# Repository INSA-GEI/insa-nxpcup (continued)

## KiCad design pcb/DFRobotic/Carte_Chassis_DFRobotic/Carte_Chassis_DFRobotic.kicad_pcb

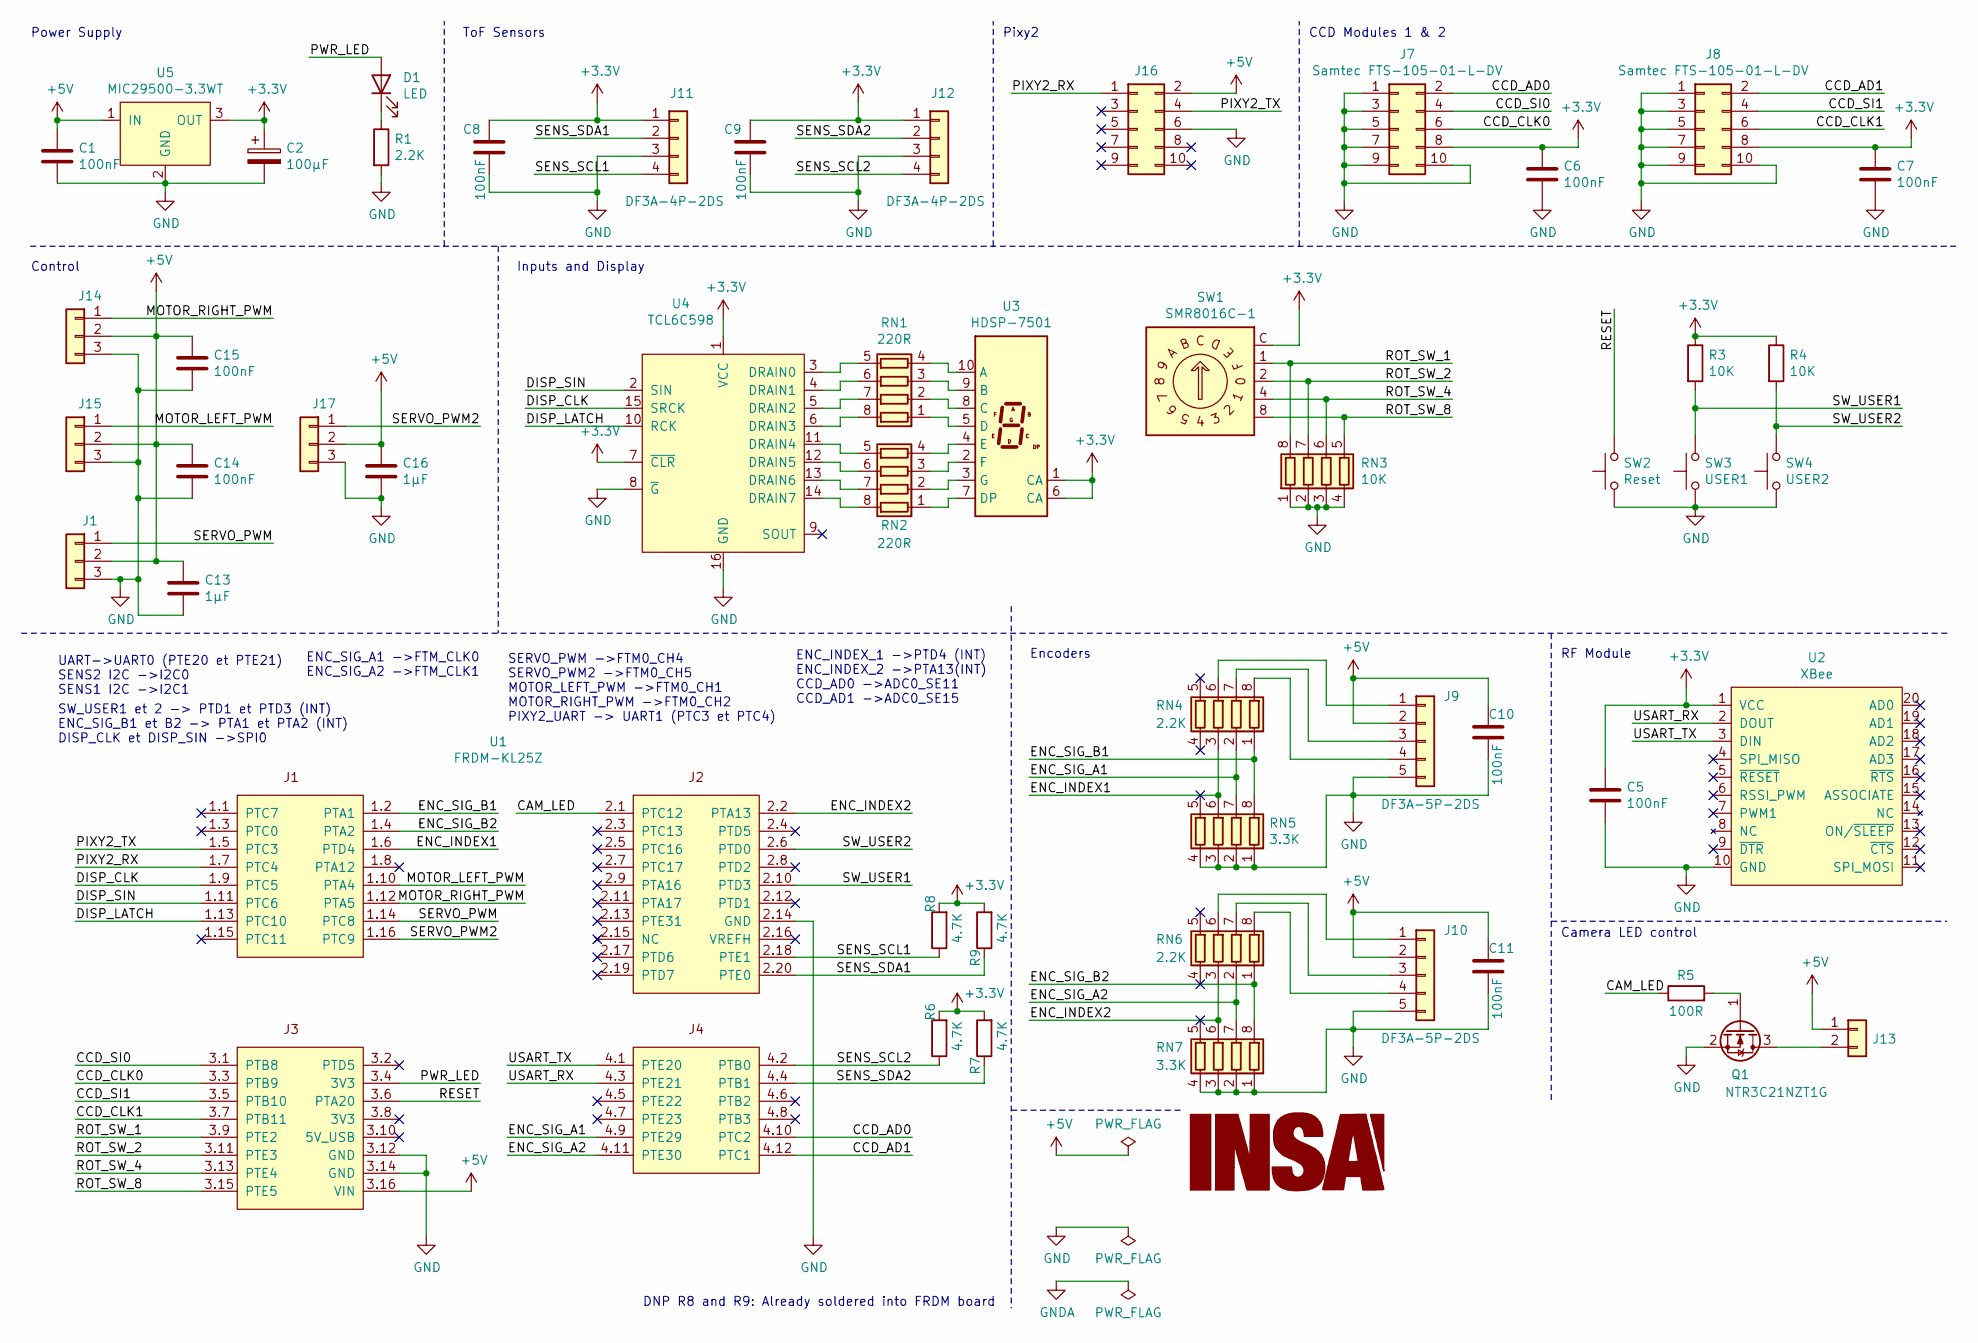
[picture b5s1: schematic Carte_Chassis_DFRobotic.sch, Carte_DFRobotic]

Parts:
C1, C5, C6, C7, C8, C9, C10, C11, C14, C15: 100nF; C_1206_3216Metric_Pad1.42x1.75mm_HandSolder
C2: 100µF; CP_Radial_D6.3mm_P2.50mm
C13, C16: 1µF; C_1206_3216Metric_Pad1.42x1.75mm_HandSolder
D1: LED; LED_1206_3216Metric_Pad1.42x1.75mm_HandSolder
J1, J14, J15, J17: Conn_01x03; PinHeader_1x03_P2.54mm_Horizontal
J7, J8: Samtec FTS-105-01-L-DV; PinHeader_2x05_P1.27mm_Vertical
J9, J10: DF3A-5P-2DS
J11, J12: DF3A-4P-2DS
J13: Conn_01x02; PinHeader_1x02_P2.54mm_Vertical
J16: Conn_02x05_Odd_Even; Multicomp_MC9A12-1034_2x05_P2.54mm_Vertical
Logo1: LOGO; insa-image
Q1: NTR3C21NZT1G; SOT-23
R1: 2.2K; R_1206_3216Metric_Pad1.42x1.75mm_HandSolder
R3, R4: 10K; R_1206_3216Metric_Pad1.42x1.75mm_HandSolder
R5: 100R; R_1206_3216Metric_Pad1.42x1.75mm_HandSolder
R6, R7, R8, R9: 4.7K; R_1206_3216Metric_Pad1.42x1.75mm_HandSolder
RN1, RN2: 220R; R_Array_Convex_4x0603
RN3: 10K; R_Array_Convex_4x0603
RN4, RN6: 2.2K; R_Array_Convex_4x0603
RN5, RN7: 3.3K; R_Array_Convex_4x0603
SW1: SMR8016C-1; Nidec_Copal_SMR-8016C
SW2: Reset; SW_PUSH_6mm_H4.3mm
SW3: USER1; SW_PUSH_6mm_H4.3mm
SW4: USER2; SW_PUSH_6mm_H4.3mm
U1: FRDM-KL25Z
U2: XBee; Xbee3
U3: HDSP-7501; HDSP-A151
U4: TCL6C598; TSSOP-16_4.4x5mm_P0.65mm
U5: MIC29500-3.3WT; TO-220-3_Vertical

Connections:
+3V3: C2.1, C5.1, C6.1, C7.1, C8.1, C9.1, J7.8, J8.8, J11.1, J12.1, R3.1, R4.1, R6.2, R7.2, R8.2, R9.2, SW1.C, U2.1 (VCC), U3.1 (CA), U3.6 (CA), U4.1 (VCC), U4.7 (~CLR), U5.3 (OUT)
+5V: C1.1, C10.1, C11.1, C13.1, C14.1, C15.1, C16.1, J1.2, J9.2, J10.2, J13.1, J14.2, J15.2, J16.2, J17.2, U1.3.16 (VIN), U5.1 (IN)
/CAM_LED: R5.1, U1.2.1 (PTC12)
/CCD_AD0: J7.2, U1.4.10 (PTC2)
/CCD_AD1: J8.2, U1.4.12 (PTC1)
/CCD_CLK0: J7.6, U1.3.3 (PTB9)
/CCD_CLK1: J8.6, U1.3.7 (PTB11)
/CCD_SI0: J7.4, U1.3.1 (PTB8)
/CCD_SI1: J8.4, U1.3.5 (PTB10)
/DISP_CLK: U1.1.9 (PTC5), U4.15 (SRCK)
/DISP_LATCH: U1.1.13 (PTC10), U4.10 (RCK)
/DISP_SIN: U1.1.11 (PTC6), U4.2 (SIN)
/ENC_INDEX1: RN4.3 (R3.1), RN5.6 (R3.2), U1.1.6 (PTD4)
/ENC_INDEX2: RN6.3 (R3.1), RN7.6 (R3.2), U1.2.2 (PTA13)
/ENC_SIG_A1: RN4.2 (R2.1), RN5.7 (R2.2), U1.4.9 (PTE29)
/ENC_SIG_A2: RN6.2 (R2.1), RN7.7 (R2.2), U1.4.11 (PTE30)
/ENC_SIG_B1: RN4.1 (R1.1), RN5.8 (R1.2), U1.1.2 (PTA1)
/ENC_SIG_B2: RN6.1 (R1.1), RN7.8 (R1.2), U1.1.4 (PTA2)
/MOTOR_LEFT_PWM: J15.1, U1.1.10 (PTA4)
/MOTOR_RIGHT_PWM: J14.1, U1.1.12 (PTA5)
/PIXY2_RX: J16.1, U1.1.7 (PTC4)
/PIXY2_TX: J16.4, U1.1.5 (PTC3)
/PWR_LED: D1.2 (A), U1.3.4 (3V3)
/RESET: SW2.2, U1.3.6 (PTA20)
/ROT_SW_1: RN3.8 (R1.2), SW1.1, U1.3.9 (PTE2)
/ROT_SW_2: RN3.7 (R2.2), SW1.2, U1.3.11 (PTE3)
/ROT_SW_4: RN3.6 (R3.2), SW1.4, U1.3.13 (PTE4)
/ROT_SW_8: RN3.5 (R4.2), SW1.8, U1.3.15 (PTE5)
/SENS_SCL1: J11.4, R8.1, U1.2.18 (PTE1)
/SENS_SCL2: J12.4, R6.1, U1.4.2 (PTB0)
/SENS_SDA1: J11.2, R9.1, U1.2.20 (PTE0)
/SENS_SDA2: J12.2, R7.1, U1.4.4 (PTB1)
/SERVO_PWM: J1.1, U1.1.14 (PTC8)
/SERVO_PWM2: J17.1, U1.1.16 (PTC9)
/SW_USER1: R3.2, SW3.2, U1.2.10 (PTD3)
/SW_USER2: R4.2, SW4.2, U1.2.6 (PTD0)
/USART_RX: U1.4.3 (PTE21), U2.2 (DOUT)
/USART_TX: U1.4.1 (PTE20), U2.3 (DIN)
GND: C1.2, C2.2, C5.2, C6.2, C7.2, C8.2, C9.2, C10.2, C11.2, C13.2, C14.2, C15.2, C16.2, J1.3, J7.1, J7.3, J7.5, J7.7, J7.9, J7.10, J8.1, J8.3, J8.5, J8.7, J8.9, J8.10, J9.5, J10.5, J11.3, J12.3, J14.3, J15.3, J16.6, J17.3, Q1.2 (S), R1.2, RN3.1 (R1.1), RN3.2 (R2.1), RN3.3 (R3.1), RN3.4 (R4.1), RN5.1 (R1.1), RN5.2 (R2.1), RN5.3 (R3.1), RN5.4 (R4.1), RN7.1 (R1.1), RN7.2 (R2.1), RN7.3 (R3.1), RN7.4 (R4.1), SW2.1, SW3.1, SW4.1, U1.2.14 (GND), U1.3.12 (GND), U1.3.14 (GND), U2.10 (GND), U4.8 (~G), U4.16 (GND), U5.2 (GND)
unnamed: D1.1 (K), R1.1
unnamed: J9.1, RN4.6 (R3.2)
unnamed: J9.3, RN4.7 (R2.2)
unnamed: J9.4, RN4.8 (R1.2)
unnamed: J10.1, RN6.6 (R3.2)
unnamed: J10.3, RN6.7 (R2.2)
unnamed: J10.4, RN6.8 (R1.2)
unnamed: J13.2, Q1.3 (D)
unnamed: Q1.1 (G), R5.2
unnamed: RN1.1 (R1.1), U3.5 (D)
unnamed: RN1.2 (R2.1), U3.8 (C)
unnamed: RN1.3 (R3.1), U3.9 (B)
unnamed: RN1.4 (R4.1), U3.10 (A)
unnamed: RN1.5 (R4.2), U4.3 (DRAIN0)
unnamed: RN1.6 (R3.2), U4.4 (DRAIN1)
unnamed: RN1.7 (R2.2), U4.5 (DRAIN2)
unnamed: RN1.8 (R1.2), U4.6 (DRAIN3)
unnamed: RN2.1 (R1.1), U3.7 (DP)
unnamed: RN2.2 (R2.1), U3.3 (G)
unnamed: RN2.3 (R3.1), U3.2 (F)
unnamed: RN2.4 (R4.1), U3.4 (E)
unnamed: RN2.5 (R4.2), U4.11 (DRAIN4)
unnamed: RN2.6 (R3.2), U4.12 (DRAIN5)
unnamed: RN2.7 (R2.2), U4.13 (DRAIN6)
unnamed: RN2.8 (R1.2), U4.14 (DRAIN7)

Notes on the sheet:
Power Supply
Control
Inputs and Display
CCD Modules 1 & 2
RF Module
Encoders
ToF Sensors
Camera LED control
DNP R8 and R9: Already soldered into FRDM board
UART->UART0 (PTE20 et PTE21) SENS2 I2C ->I2C0 SENS1 I2C ->I2C1
ENC_SIG_A1 ->FTM_CLK0 ENC_SIG_A2 ->FTM_CLK1
SERVO_PWM ->FTM0_CH4 SERVO_PWM2 ->FTM0_CH5 MOTOR_LEFT_PWM ->FTM0_CH1 MOTOR_RIGHT_PWM ->FTM0_CH2 PIXY2_UART -> UART1 (PTC3 et PTC4)
ENC_INDEX_1 ->PTD4 (INT) ENC_INDEX_2 ->PTA13(INT) CCD_AD0 ->ADC0_SE11 CCD_AD1 ->ADC0_SE15
SW_USER1 et 2 -> PTD1 et PTD3 (INT) ENC_SIG_B1 et B2 -> PTA1 et PTA2 (INT) DISP_CLK et DISP_SIN ->SPI0
Pixy2

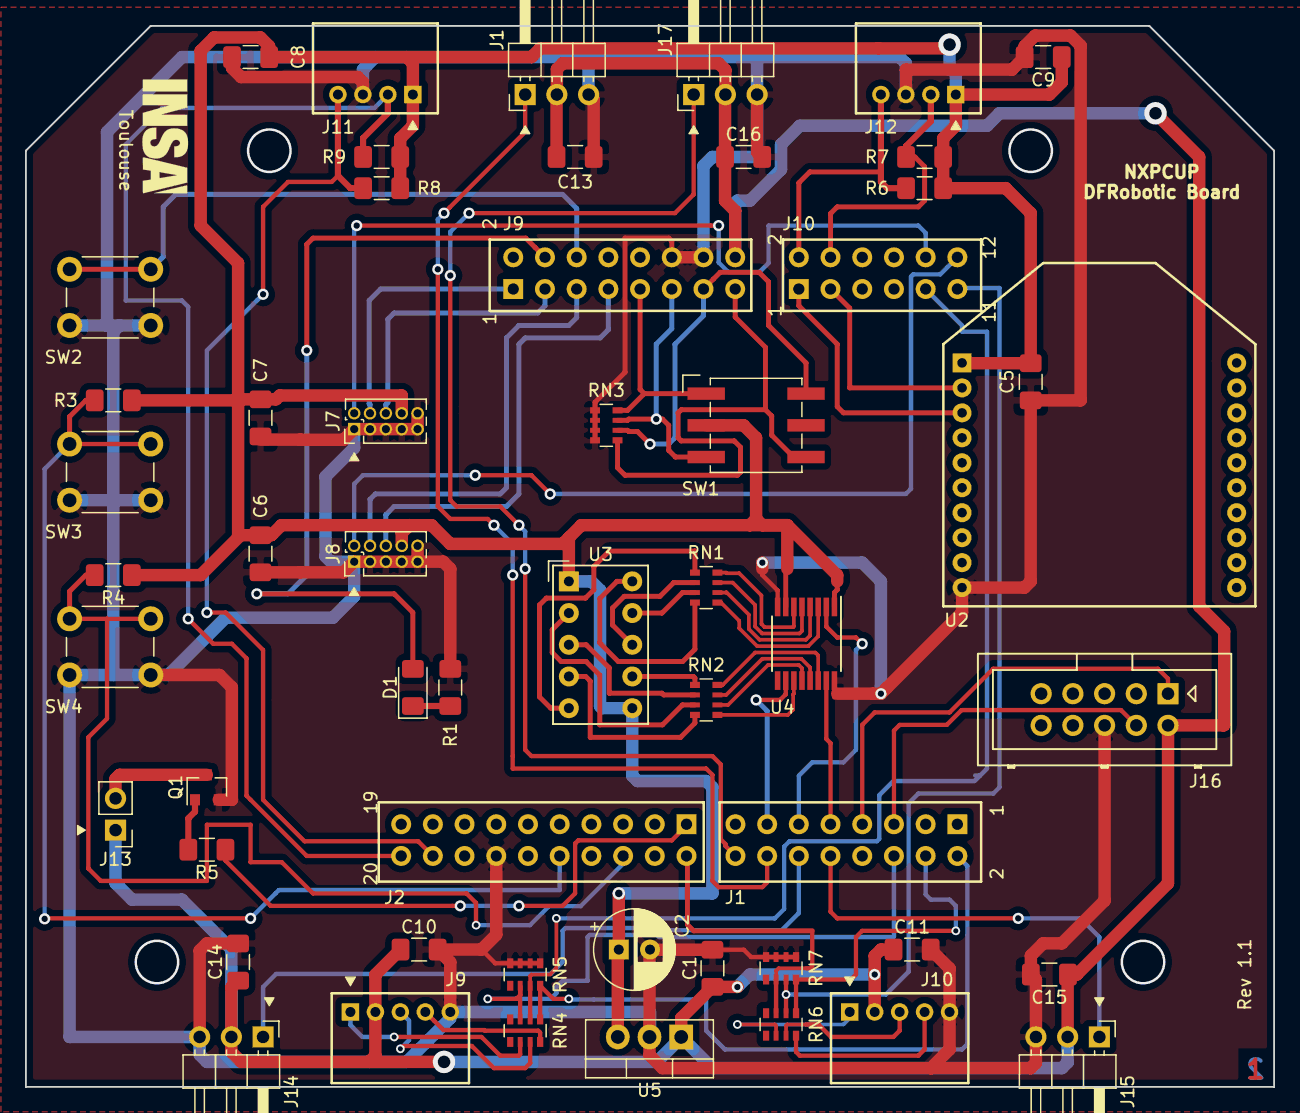
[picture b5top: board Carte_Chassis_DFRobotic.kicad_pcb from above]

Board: 2 copper layers, 100.0 x 85.0 mm, 52 parts (1 on the bottom side), 64 nets.

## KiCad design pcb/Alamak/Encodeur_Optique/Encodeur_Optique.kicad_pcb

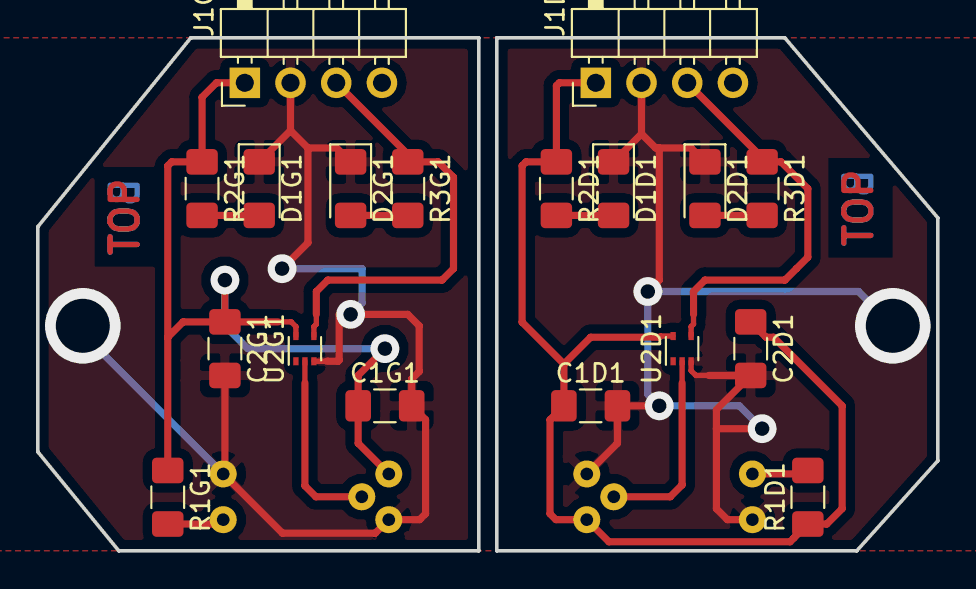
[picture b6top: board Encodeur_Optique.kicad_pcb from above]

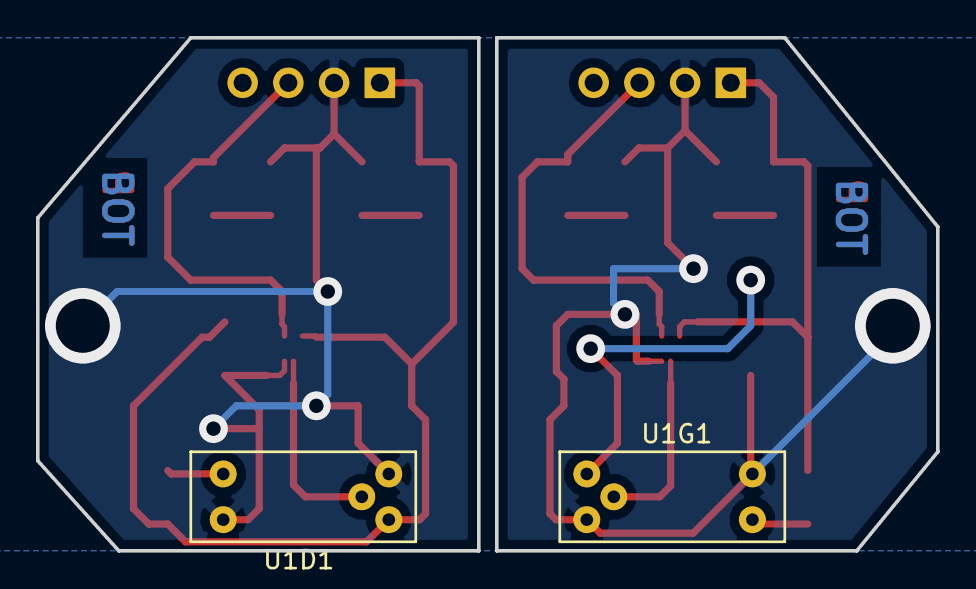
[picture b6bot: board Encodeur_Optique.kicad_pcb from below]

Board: 2 copper layers, 50.0 x 28.5 mm, 20 parts (2 on the bottom side), 12 nets.

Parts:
C1D1, C1G1, C2D1, C2G1: 100nF; C_1206_3216Metric_Pad1.42x1.75mm_HandSolder
D1D1, D1G1: Led Verte; LED_1206_3216Metric_Pad1.42x1.75mm_HandSolder
D2D1, D2G1: Led Rouge; LED_1206_3216Metric_Pad1.42x1.75mm_HandSolder
J1D1, J1G1: Conn_01x04; PinHeader_1x04_P2.54mm_Horizontal
R1D1, R1G1, R2D1, R2G1, R3D1, R3G1: R; R_1206_3216Metric_Pad1.42x1.75mm_HandSolder
U1D1, U1G1: GP1A52LRJ00F
U2D1, U2G1: 74LVC1G17; SOT-553

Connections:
/OUT_D: J1D1.3, R3D1.1, U2D1.4
/OUT_G: J1G1.3, R3G1.1, U2G1.4
GND: C1D1.2, C1G1.2, C2D1.2, C2G1.2, D1D1.1, D1G1.1, D2D1.1, D2G1.1, J1D1.2, J1G1.2, U1D1.2, U1D1.5, U1G1.2, U1G1.5, U2D1.3, U2G1.3
unnamed: D1D1.2, R2D1.2
unnamed: D1G1.2, R2G1.2
unnamed: D2D1.2, R3D1.2
unnamed: D2G1.2, R3G1.2
unnamed: R1D1.2, U1D1.1
unnamed: R1G1.2, U1G1.1
unnamed: U1D1.4, U2D1.2
unnamed: U1G1.4, U2G1.2
VCC: C1D1.1, C1G1.1, C2D1.1, C2G1.1, J1D1.1, J1G1.1, R1D1.1, R1G1.1, R2D1.1, R2G1.1, U1D1.3, U1G1.3, U2D1.5, U2G1.5

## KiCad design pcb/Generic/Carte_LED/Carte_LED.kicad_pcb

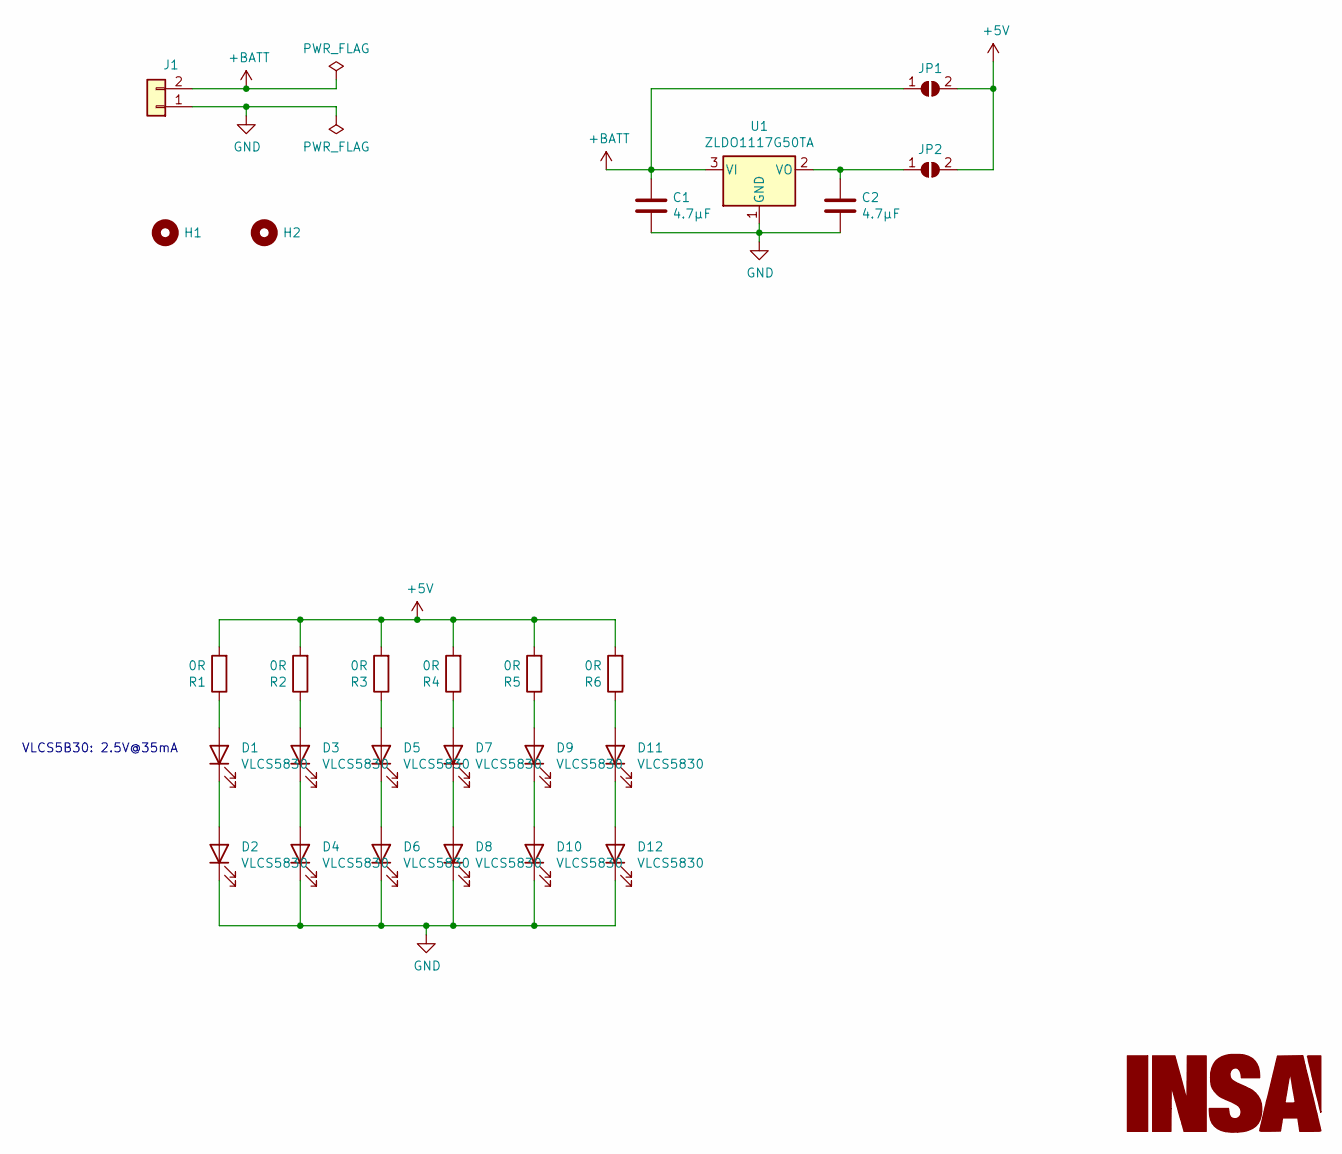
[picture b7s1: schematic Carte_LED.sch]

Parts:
C1, C2: 4.7µF; C_1206_3216Metric_Pad1.42x1.75mm_HandSolder
D1, D2, D3, D4, D5, D6, D7, D8, D9, D10, D11, D12: VLCS5830; LED_D5.0mm_Clear
G1: LOGO; insa-image
H1, H2: MountingHole; MountingHole_2.7mm_M2.5
J1: Conn_01x02; PinHeader_1x02_P2.54mm_Vertical
JP1, JP2: SolderJumper_2_Open; SolderJumper-2_P1.3mm_Open_RoundedPad1.0x1.5mm
R1, R2, R3, R4, R5, R6: 0R; R_Axial_DIN0309_L9.0mm_D3.2mm_P2.54mm_Vertical
U1: ZLDO1117G50TA; SOT-223-3_TabPin2

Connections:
+5V: JP1.2 (B), JP2.2 (B), R1.2, R2.2, R3.2, R4.2, R5.2, R6.2
+BATT: C1.1, J1.2, JP1.1 (A), U1.3 (VI)
GND: C1.2, C2.2, D2.1 (K), D4.1 (K), D6.1 (K), D8.1 (K), D10.1 (K), D12.1 (K), J1.1, U1.1 (GND)
unnamed: C2.1, JP2.1 (A), U1.2 (VO)
unnamed: D1.1 (K), D2.2 (A)
unnamed: D1.2 (A), R1.1
unnamed: D3.1 (K), D4.2 (A)
unnamed: D3.2 (A), R2.1
unnamed: D5.1 (K), D6.2 (A)
unnamed: D5.2 (A), R3.1
unnamed: D7.1 (K), D8.2 (A)
unnamed: D7.2 (A), R4.1
unnamed: D9.2 (A), R5.1
unnamed: D9.1 (K), D10.2 (A)
unnamed: D11.1 (K), D12.2 (A)
unnamed: D11.2 (A), R6.1

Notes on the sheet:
VLCS5B30: 2.5V@35mA

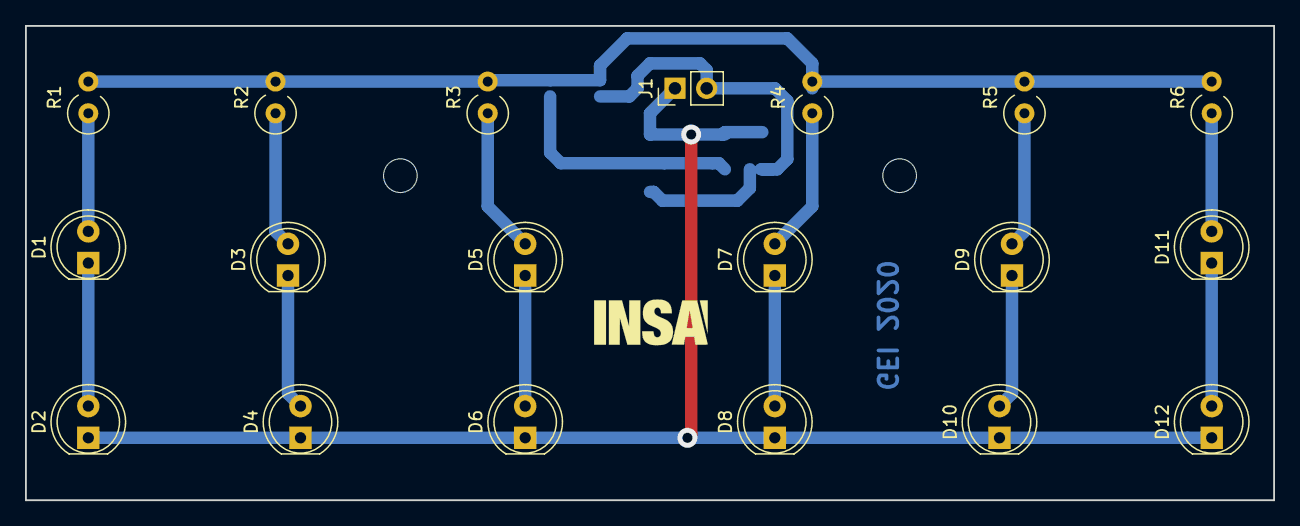
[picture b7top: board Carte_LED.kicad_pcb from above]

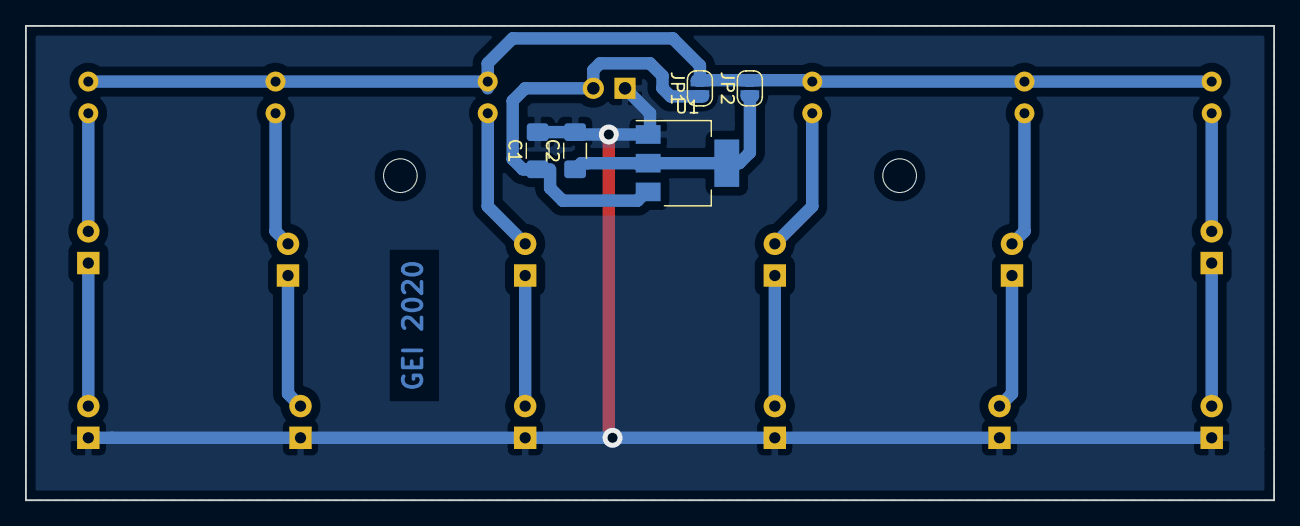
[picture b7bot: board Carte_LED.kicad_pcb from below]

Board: 2 copper layers, 100.0 x 38.0 mm, 27 parts (5 on the bottom side), 16 nets.

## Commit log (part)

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2019-03-05 Added Matlab addons tutorial
2019-03-08 Add functionnal base Code
2019-03-08 Add Gloabal Defines Vincent
2019-03-08 reduce the gitignore list
2019-03-09 cleanup the repo. Sources are now in 'Sources' folder ;)
2019-03-13 add some codes
    Some codes on codewarrior
2019-03-13 Add the git installation link
2019-03-13 Reorganize the repo
2019-03-14 update_detection_type
    creation de la fonction
2019-03-16 oui oui oui
2019-03-18 add a processor expert project
2019-03-18 change name
2019-03-25 remove broken folder
2019-03-25 Create Memo_2019
2019-03-25 Rename Memo_2019 to Memo_2019.md
2019-05-19 final update
2019-07-23 modification du fichier .gitignore
2019-07-29 Essai de Freecad, pas concluant
2019-07-30 Ajout de fichiers DXF et DWG
2019-07-31 Modelisation sous Inventor bien avancée: manque la camera
2019-07-31 Cartes En cours de conception
2019-08-29 demarrage carte capteurs
2019-08-29 Petites corrections
2019-08-29 Ajout du XBEE
2019-09-04 sauvegarde intermediaire
2019-09-05 ajout des versions sur les cartes
2019-09-06 Ajout des bon rendu des cartes puissance et capteurs, mais crash d'inventor
2019-10-03 mise a jour des projets Kicad
2019-10-11 Correction sur carte capteur + realisation des pieces du circuit sous LibreCad/InkScape
2019-10-18 correction sur carte capteur
2019-11-28 Added schematic in pdf format
2019-11-28 Added schematic
2019-12-03 -mbutton test complete
2019-12-03 debut : led rgb et afficheur 7 segments
2019-12-03 updated .gitignore for CodeWarrior files
2019-12-03 removed temp files accidentally pushed
2019-12-03 debug cleanup
2019-12-04 ring buffer and debug uart transmit working ! Also PLL is fixed at 48MHz
2019-12-05 Updated mins and baudrate
2019-12-07 defines for uart type
2019-12-07 created motor test project
2019-12-07 only one pwm channel working
2019-12-08 servo
2019-12-08 servo rework
2019-12-10 motor enable and direction fixed, right motor still not moving
2019-12-10 removed debug class from servo project
2019-12-27 motor working !
2019-12-27 servo funcs
2020-01-13 Started direction project
2020-01-17 creation d'une carte camera et d'une carte pour els led
2020-01-21 -mcamera working !
2020-01-22 -mcreated image processing folder
2020-01-27 -mImage processing
2020-01-28 -mencoder simplify
2020-01-28 update_encodeur
2020-01-29 removed extra encoder project
2020-01-29 updated Encoder to use class and return acutal speed
2020-01-30 ajout de la carte chassi DFRobotics + creation d'une nouvelle carte led + creation d'une carte capteur pour DFRobotic + correction de l'alimentation en 5V des encodeurs sur DFRobotic (carte Landzo a 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
2020-01-30 Branche evolution-HW a merger sur evo60
2020-01-30 Suppression de fichiers backup et doublons
2020-02-01 movement intergrating encoder
2020-02-01 direction speed controller seems to work : to test in real
2020-02-02 Image processing takes approx. 940us. Project cleanup
2020-02-03 graph vitesse/PWM
2020-02-04 recharge battery
2020-02-05 low power timer config
2020-02-06 Ajout des regles NXPCup 2020 (V1)
2020-02-06 lptmr + battery
2020-02-07 sandbox test complete
2020-02-07 macro LED camera
2020-02-07 Changement de capteur pour les encodeurs DFRobot
2020-02-13 servo excel
2020-02-13 add_flash_files
2020-02-17 detection finish line + variation of thresholds for the edges
2020-02-24 test mémoire virage
2020-02-25 modif linedetection
2020-02-26 NXP_Dry tests
2020-02-26 end of finish line
2020-03-01 push NXP_Dry Equipe 2
2020-03-03 azerty
2020-12-12 Mis à jour du code version de Raph
2020-12-12 Test detection lignes + régul vitesse + amélioration différentiel
2020-12-12 Choix du mode de Debug au clavier via Putty
2020-12-14 test1
2020-12-14 Resolution prblm
2020-12-14 OK v=fct(linéaire)
2020-12-15 Ajout de code dans ImageProcessing par Carole et Mathilde
    Ajout de fonctions de visionnage des données brutes ou traitées de la caméra (display_camera_data) pour utilisation dans serial port plotter.
    /!\ Raph il y avait un warning sur le define SERVO_MAX_LEFT_ANGLE et même chose sur le SERVO_MAX_RIGHT_ANGLE. J'ai commenté ces deux lignes pour le code compile sans warning mais il faut voir si elle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
2020-12-15 Ajout ESP
2020-12-15 ESP avec temps d'activation : à tester
2020-12-16 Comment Image Process
2020-12-17 marche arrière
2020-12-17 Mise à jour du main
2020-12-17 Ajout Process_camera
2020-12-17 freinage
2020-12-17 fin ajout process_camera
2020-12-17 débug affichage data camera sur uart
    Dans le main pour la boucle i : mettre un seuil assez haut sinon écriture et lecture en même temps entre capture et display_camera_data qui fait un hardfault
2020-12-21 Test PID vitesse + ajout PID direction à la place du PI
2020-12-21 QQ modifs
2020-12-21 modifs freiange
2021-01-05 trajectoire adaptative
2021-01-06 algo detect ligne OK
2021-01-06 TEst detect ligne de fin
2021-01-06 Ajout commentaires
2021-01-06 Ajout commentaires Car_control.cpp
2021-01-06 Correctoin pblm freinage max
2021-01-06 Gros ménage dans ImageProcessing
2021-01-06 LED Bleue #JACKIE_TUNING!
2021-01-07 PI pour les motors OK
2021-01-07 modifs 18 décembre ImageProc
2021-01-07 PI moteurs arrières OK!
2021-01-08 PI moteurs OK / marche av et ar
2021-01-12 Tout est ok! amélioartion en attente
2021-01-25 QQ changements
2021-01-27 Ajout Control global de la fréquence d'IT depuis le main
2021-01-29 Test New IT
2021-02-03 Modifications fichiers team2
2021-02-03 Creation Obstacle Detector files
    Creation of the files for the obstacle detection with the long distance ranging sensor VL53L1X. Adding of the datasheets and library information for this sensor.
2021-02-03 Echantillonnage plus rapide OK 500Hz OK
2021-02-04 PID pour la direction ok => réglages des valeurs en cours
2021-02-04 Modifs accélération, calcul de Vset plus lent
2021-02-08 OK pour compet
2021-02-08 Ajout fonctionnalité 0xA -> affichage de la camera, valeurs min/max et le threshold
2021-02-10 MenageIMGPROC2
2021-02-11 Ajout commentaires ImageProcessing.cpp par Romain
2021-02-17 Mesure de la vitesse positive ou négative
2021-02-23 Ok pour compet!
2021-02-23 A tester Anti-soleil
2021-02-24 Non concluant
2021-02-24 MODE1 sans sol et MODE 2 tentative avec soleil
2021-02-24 OK pour compet + Bouton de démarrage ok
2021-02-24 modif readme
2021-02-25 clean up ok
2021-02-25 algo 2 pas ouf
2021-02-25 diminution du diff au freinage, la voiture glisse bcp
2021-03-02 Petit changement detection ligne de fin
2021-03-03 Ajout CalculMilieu pour functionning_mode 0xA -> VOITURE QUI ROULE
2021-03-03 Mauvaise Fe
2021-03-03 OK PI Moteur
2021-03-03 Modifications code - Voiture remarche - Camera baissee
2021-03-04 Réglage
2021-03-09 Ajout des fichiers de détection d'osbtacles
    Ajout de Obstacle_detection.h et .cpp pour le capteur de distance
2021-03-11 Freinage OK à moins de 2m
2021-03-11 OK attentes améliorations
2021-03-16 Tests ok sur les fonctions basiques de Sensor
    En cours d'ajout des fonctions d'interface avec l'API sur platform.c
2021-03-19 VOITURE QUI FONCTIONNE - Modif sur Car_control, déplacement de la batterie, déplacement de la camera, intégration de la nouvelle IT
2021-03-19 ajout des dernières fonctions de platform
    fonctions à tester avec les méthodes de Sensor
2021-03-24 Modifications du code //// Ajout moyennage du threshold sur 100 points pour atténuer les différences de threshold, voiture plus smooth //// Ajout ecart type pour éliminer les valeurs trop différentes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
2021-03-24 Ajouts debug I2C
2021-03-27 Servo en attente
2021-03-27 Reset pointeur
2021-03-27 Ajout include dans PID.h
2021-03-27 Ajout Te_PID
2021-03-27 VOITURE QUI ROULE AVEC LE PID
2021-03-30 minor changes
2021-03-30 Probleme période IT
2021-04-02 ne link pas (probleme de code mixte C/C++), mais les peripheriques TPM utilisent maintenant la HAL
2021-04-03 Efface
2021-04-03 VOITURE QUI ROULE - Finitions du PID, ajout Mode A (roule directement) et B (roule si on appuie sur barre espace) et tests avec les lumieres
2021-04-03 Ajout mode A, B et C pour slow, normal et Fast - Bonnification du code, ajout de commentaires et deplacement des define pour le PID, speed et angle wheels dans le .c pour les modifier en fonction du 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
2021-04-08 recup projet Romain
2021-04-09 I2C et tick compteur pour le TOF opérationnel
2021-04-11 Detection obstacle OK
2021-04-13 Code pour la course v1
2021-04-16 demarrage des PCB basé sur LPC43xx
2023-03-03 Portage du projet 2019-2020/Equipe2/NXP_Dry sous mcuexpresso (projet 2019-2020/Equipe2/NXP-DRY-2023)
2023-04-20 Projet initial sur carte FRDM-K32L3A6, multicoeur
2023-05-10 Ajout de la voiture ROB0170 de dfrobot
2023-05-31 travail en cours sur l'adaptation du chassis aux nouveaux moteurs
2023-07-06 Modelisation de la voiture terminée, pieces à tester
2023-11-26 Created First 2023 Team
2023-11-30 add readme to 23_24
2023-11-30 Creation projet MCUxpresso
2023-11-30 Add gitignore for 23-24
2023-12-28 Remove project files from git
2023-12-30 Add readme, guides and a folder for buggy's drivers
2024-01-18 STABLE : add drivers for DC_motors, tested, worked
2024-01-18 add documentation for DC motor on KL25Z and change gitignore to include buggy folder
2024-01-22 Add missing documentation
2024-01-25 Change define functions to inline in dc motor code, untested
2024-01-25 STABLE: update for dc motor code tested
2024-01-25 driver encoder done, test done, go in use
2024-01-25 add driver_encoder done in the project
2024-01-26 Ajout des méthodes capture, affiche_image et init dans Image_Processing. Testé indépendant de la classe ImageProcessing et fonctionne.
2024-01-26 Add doc to ImageProcessing branch
2024-01-26 driver_movement version 2 : control law for the mortor speed OK
2024-01-27 Added delay functions
2024-01-30 driver servo version 1 : need to define center position, driver movement version 2 : complete function movement_set
2024-02-02 Adapte motor and encoder driver to Cpp, add a info to readme and guides
2024-02-02 Ajout commentaire ImageProcessing. Modification fct affiche_image pour clarifier l'affichage
2024-02-02 debug not completed yet, driver_servo done
2024-02-02 Add mouvement driver to main_test
2024-02-02 Ajout de la fct affiche_edge. Test des fct de traitements de l'image
2024-02-06 First attemp to test all component together, get code from ImageProg commit 1361604b
2024-02-06 Add main source code for buggy, not works
2024-02-07 done mouvement, start driver_debug
2024-02-07 car runs correctly for the left side, need to symmetrize two sides of the servomotor
2024-02-14 Faible vitesse et oscillation. Peu de stabilité dans les virages. Sorties de piste +++
2024-02-16 Fonctionne avec deux cameras
2024-02-17 add code to slow down when turning corners, not working well
2024-02-21 Init branch for testing bluetooth bee
2024-02-21 Receive on PC OK, add python code to print data on PC
2024-03-13 control not completed, wait for the completion of mechanical part
2024-03-15 Transfer camera data OK with DMA
2024-04-05 STABLE : 1 LiDAR on J11 (to inverse SCL1 and SDA1)
2024-04-10 Add functions to set camera gain and change servo parameters
2024-04-12 Print data to terminal work correctly for image data. Able to turn on/off motor remotely.
2024-04-22 Show others camera data in the terminal of the PC - Not fully tested yet
2024-04-22 Add guide for user interface and parameters changing, in dev
2024-04-24 Essai code ADC interrupt
2024-04-24 Fix speed regulation loop, Add speed monitoring, Delete unused image process mode
2024-04-27 version : 2 different gains of the servomotor angle and 2 different differential values
2024-04-27 differential calcul, roadmiddle modification
2024-04-28 add filter pass-bas, OK turn left, KO turn right
2024-04-29 New param with turn threshold
2024-04-29 Voiture rouge marche a gauche, régler le diiérentielle pour pouvoir tourner a droite
2024-10-19 save all works of team 23-24 to git
2026-03-23 Remontée des pieces meca
2026-03-25 Creation d'un projet car-control-frdmmcxn236 créé "from scratch" avec la HAL a jour et dans lequel les fichiers de gestion camera et ecran du projet dm-mcxn236-camera-interface-by-smartdma ont été im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
2026-03-25 WIP ajout du fichier mex et fiabilisation de la generation auto de configuration
2026-03-27 Wip Creation des taches, des buffers images et d'algo de traitement (pas fonctionnel)
2026-04-16 Wip integration lors de la NXPCUP
